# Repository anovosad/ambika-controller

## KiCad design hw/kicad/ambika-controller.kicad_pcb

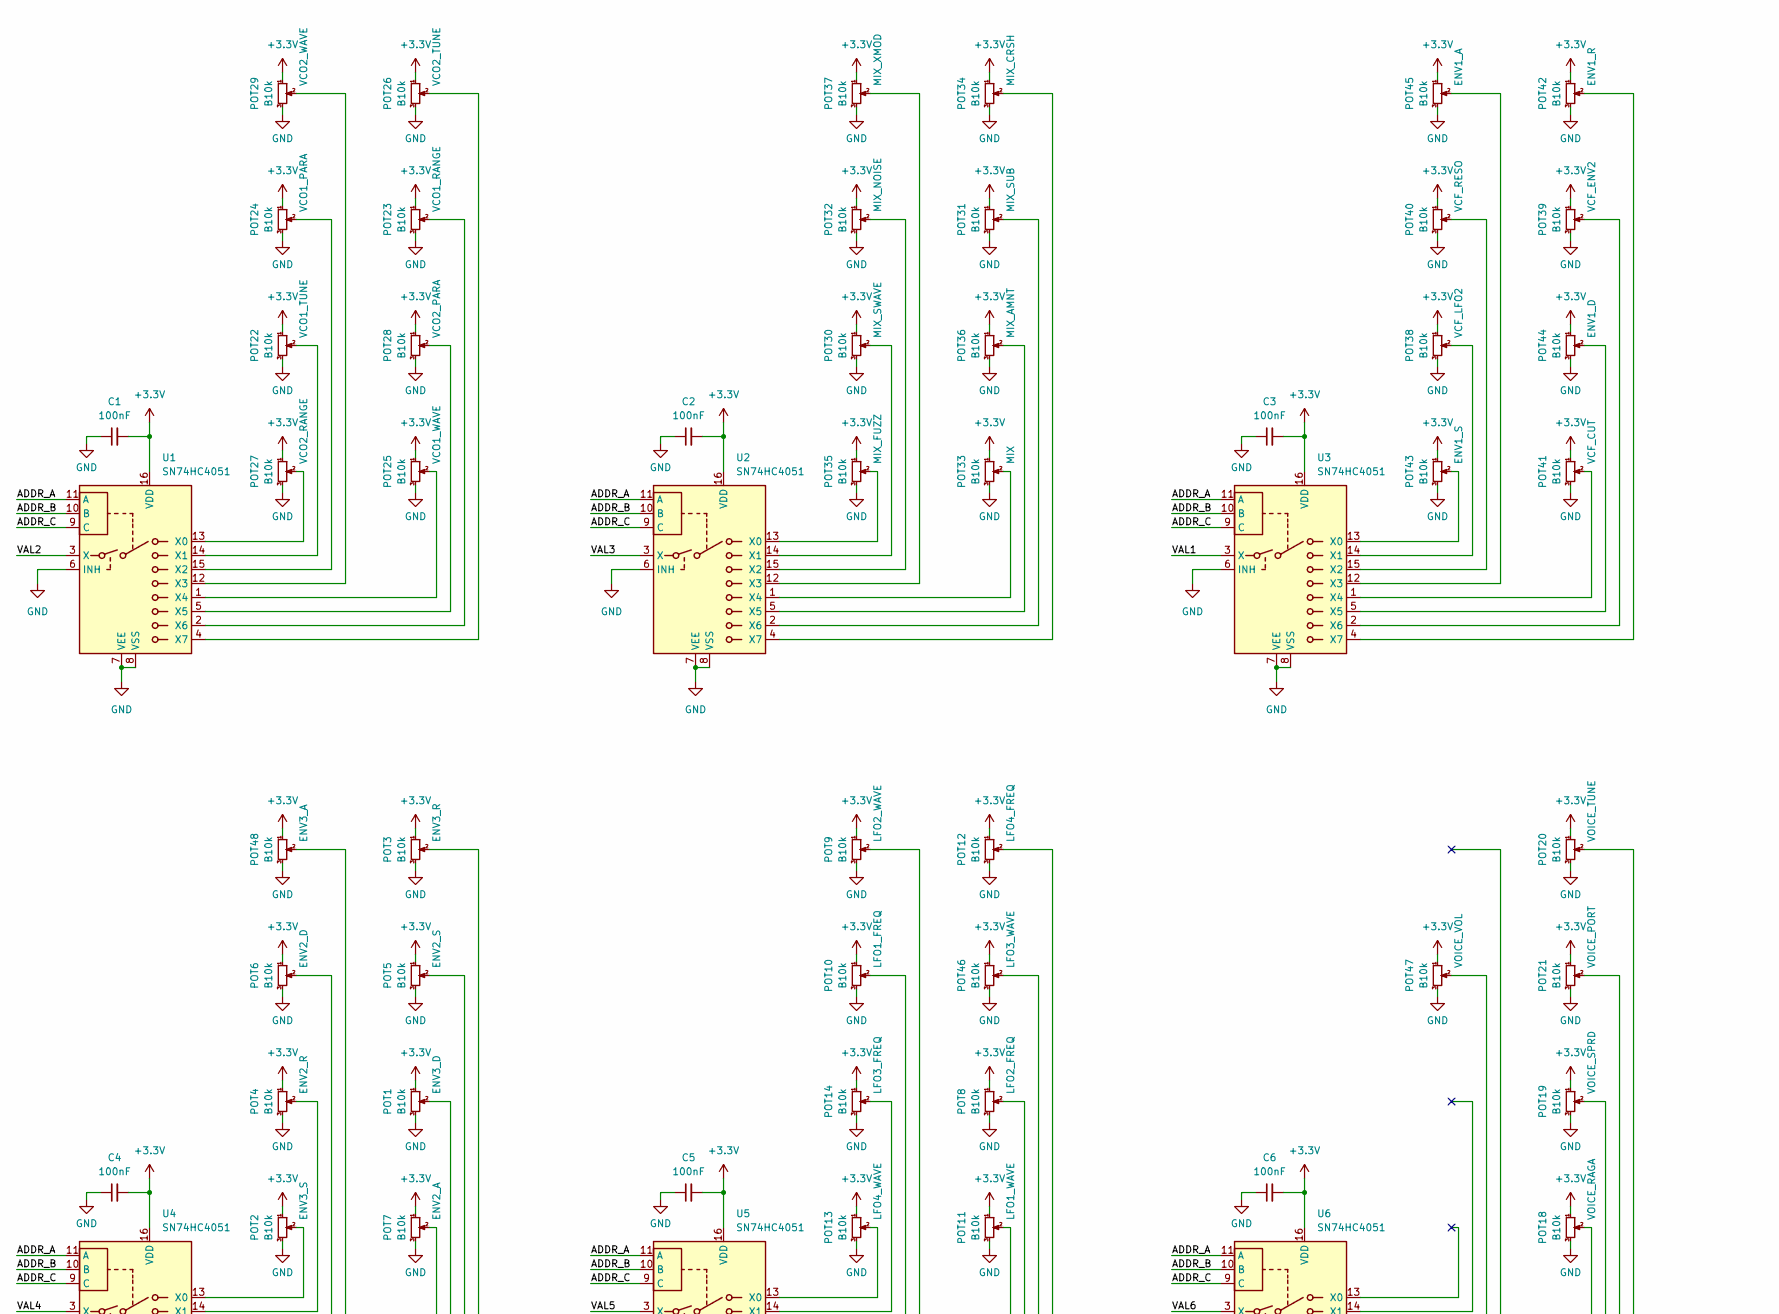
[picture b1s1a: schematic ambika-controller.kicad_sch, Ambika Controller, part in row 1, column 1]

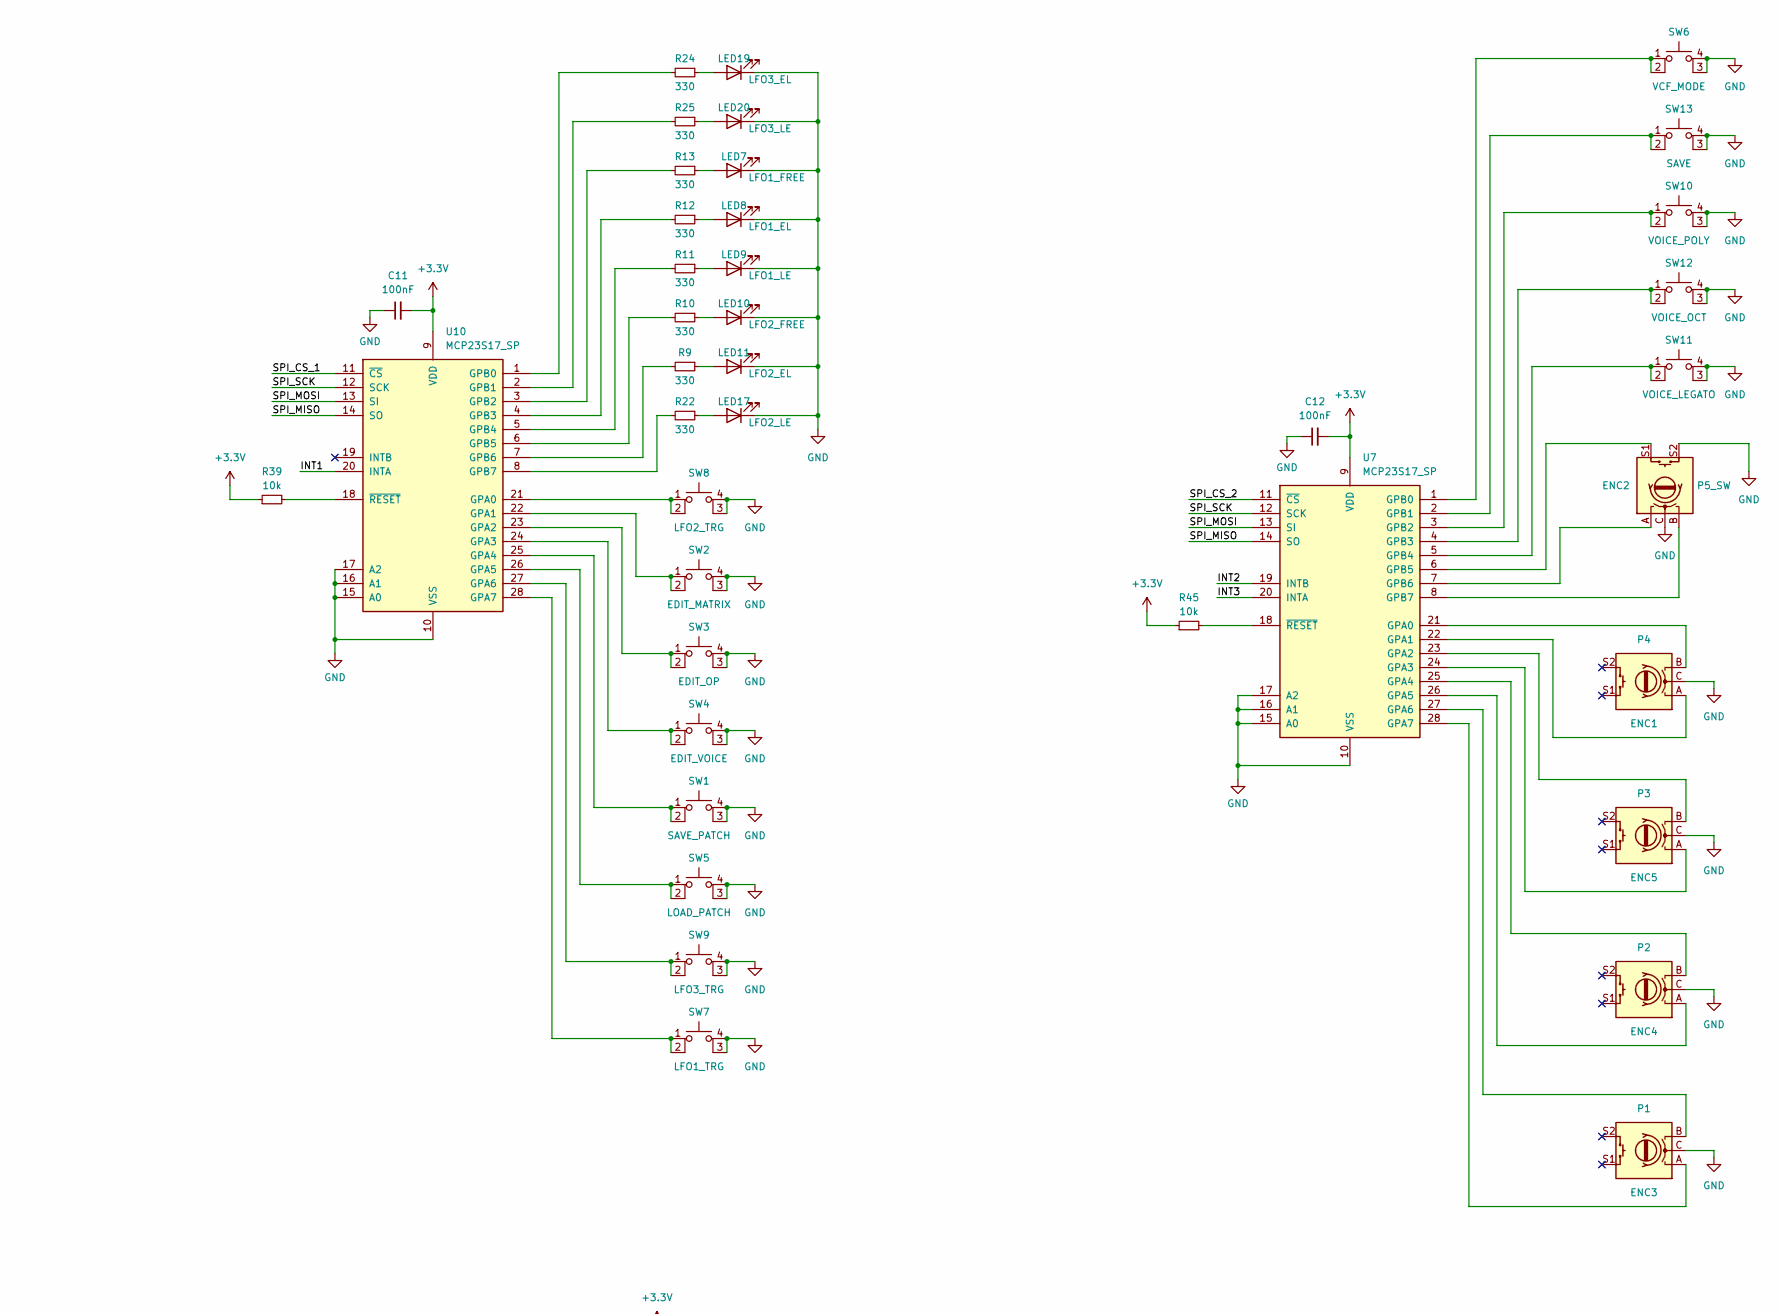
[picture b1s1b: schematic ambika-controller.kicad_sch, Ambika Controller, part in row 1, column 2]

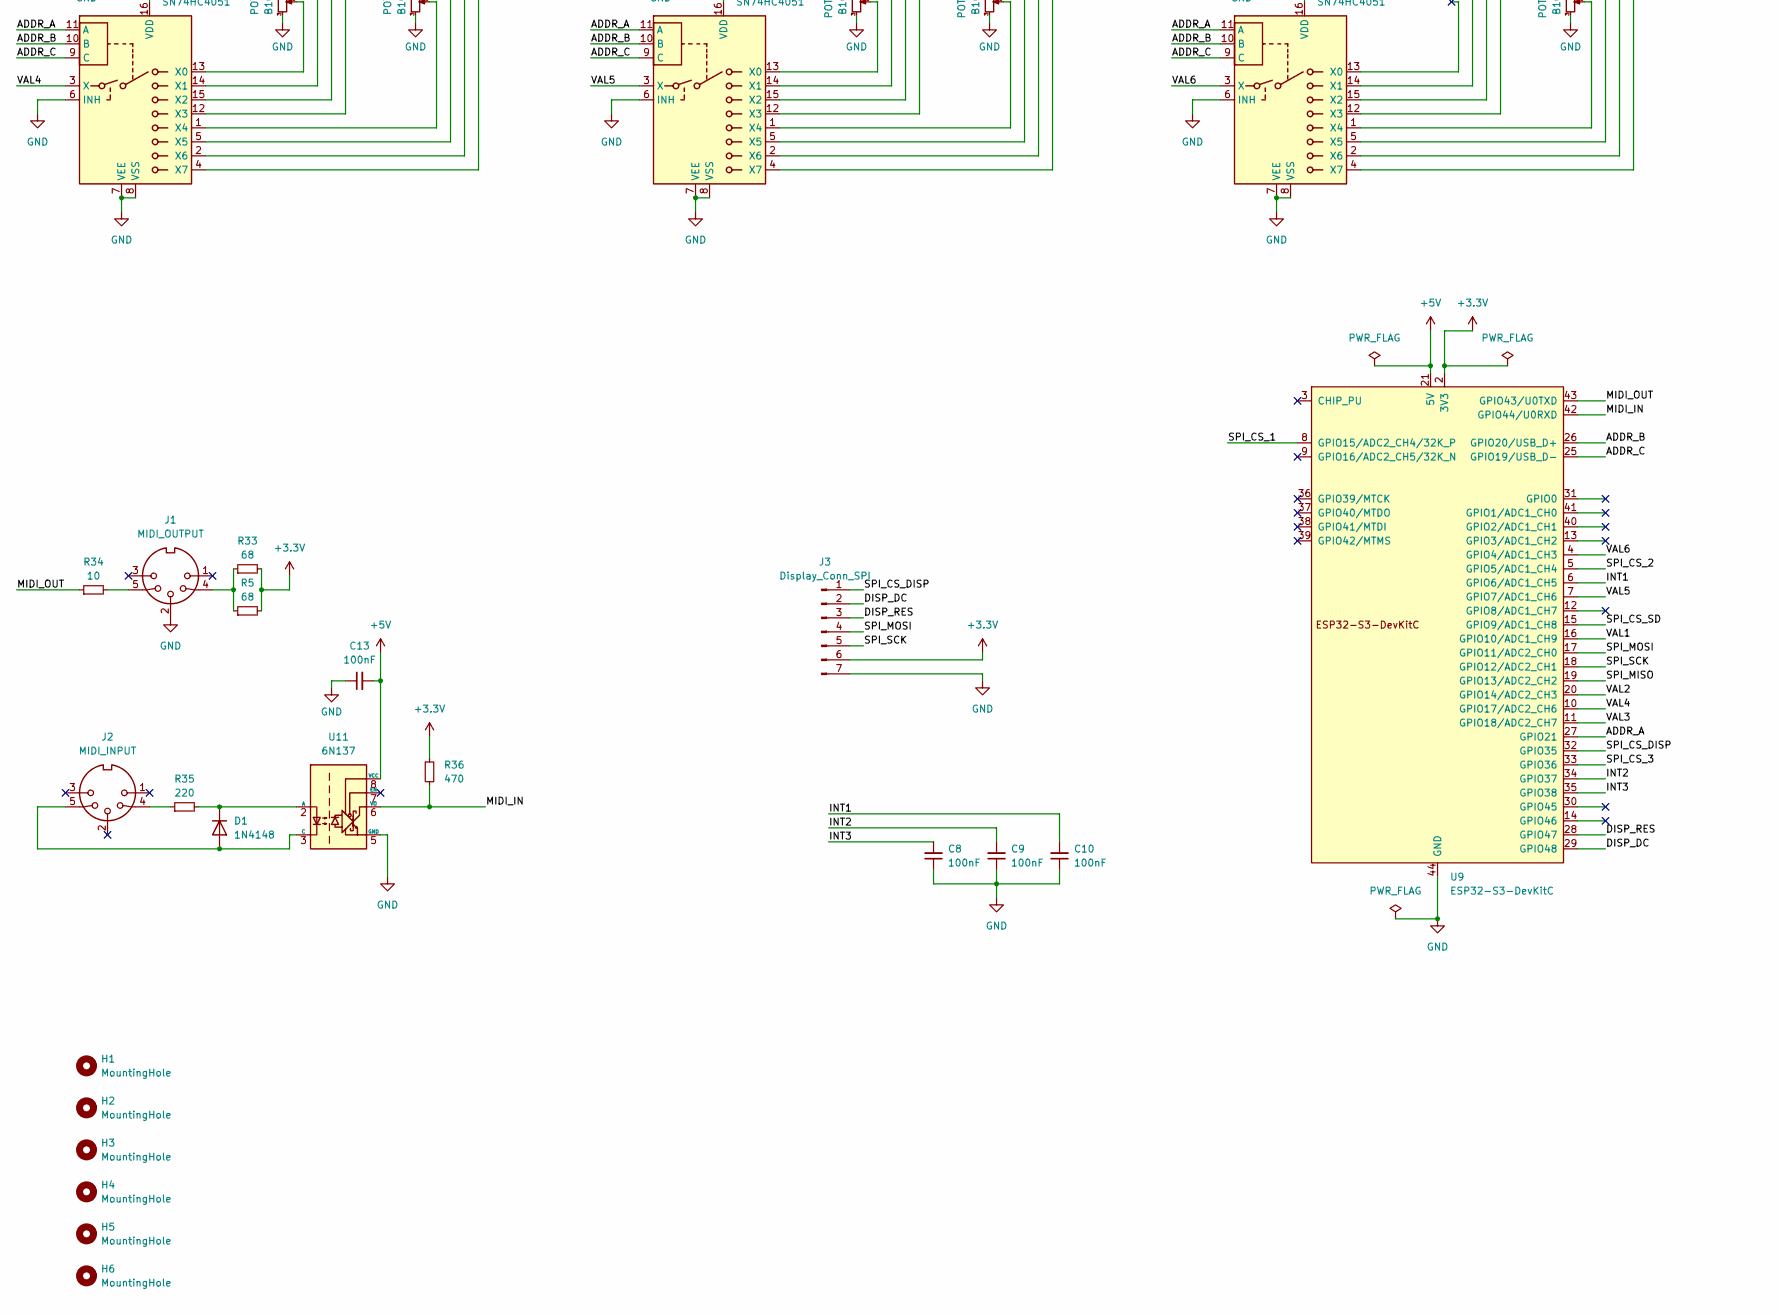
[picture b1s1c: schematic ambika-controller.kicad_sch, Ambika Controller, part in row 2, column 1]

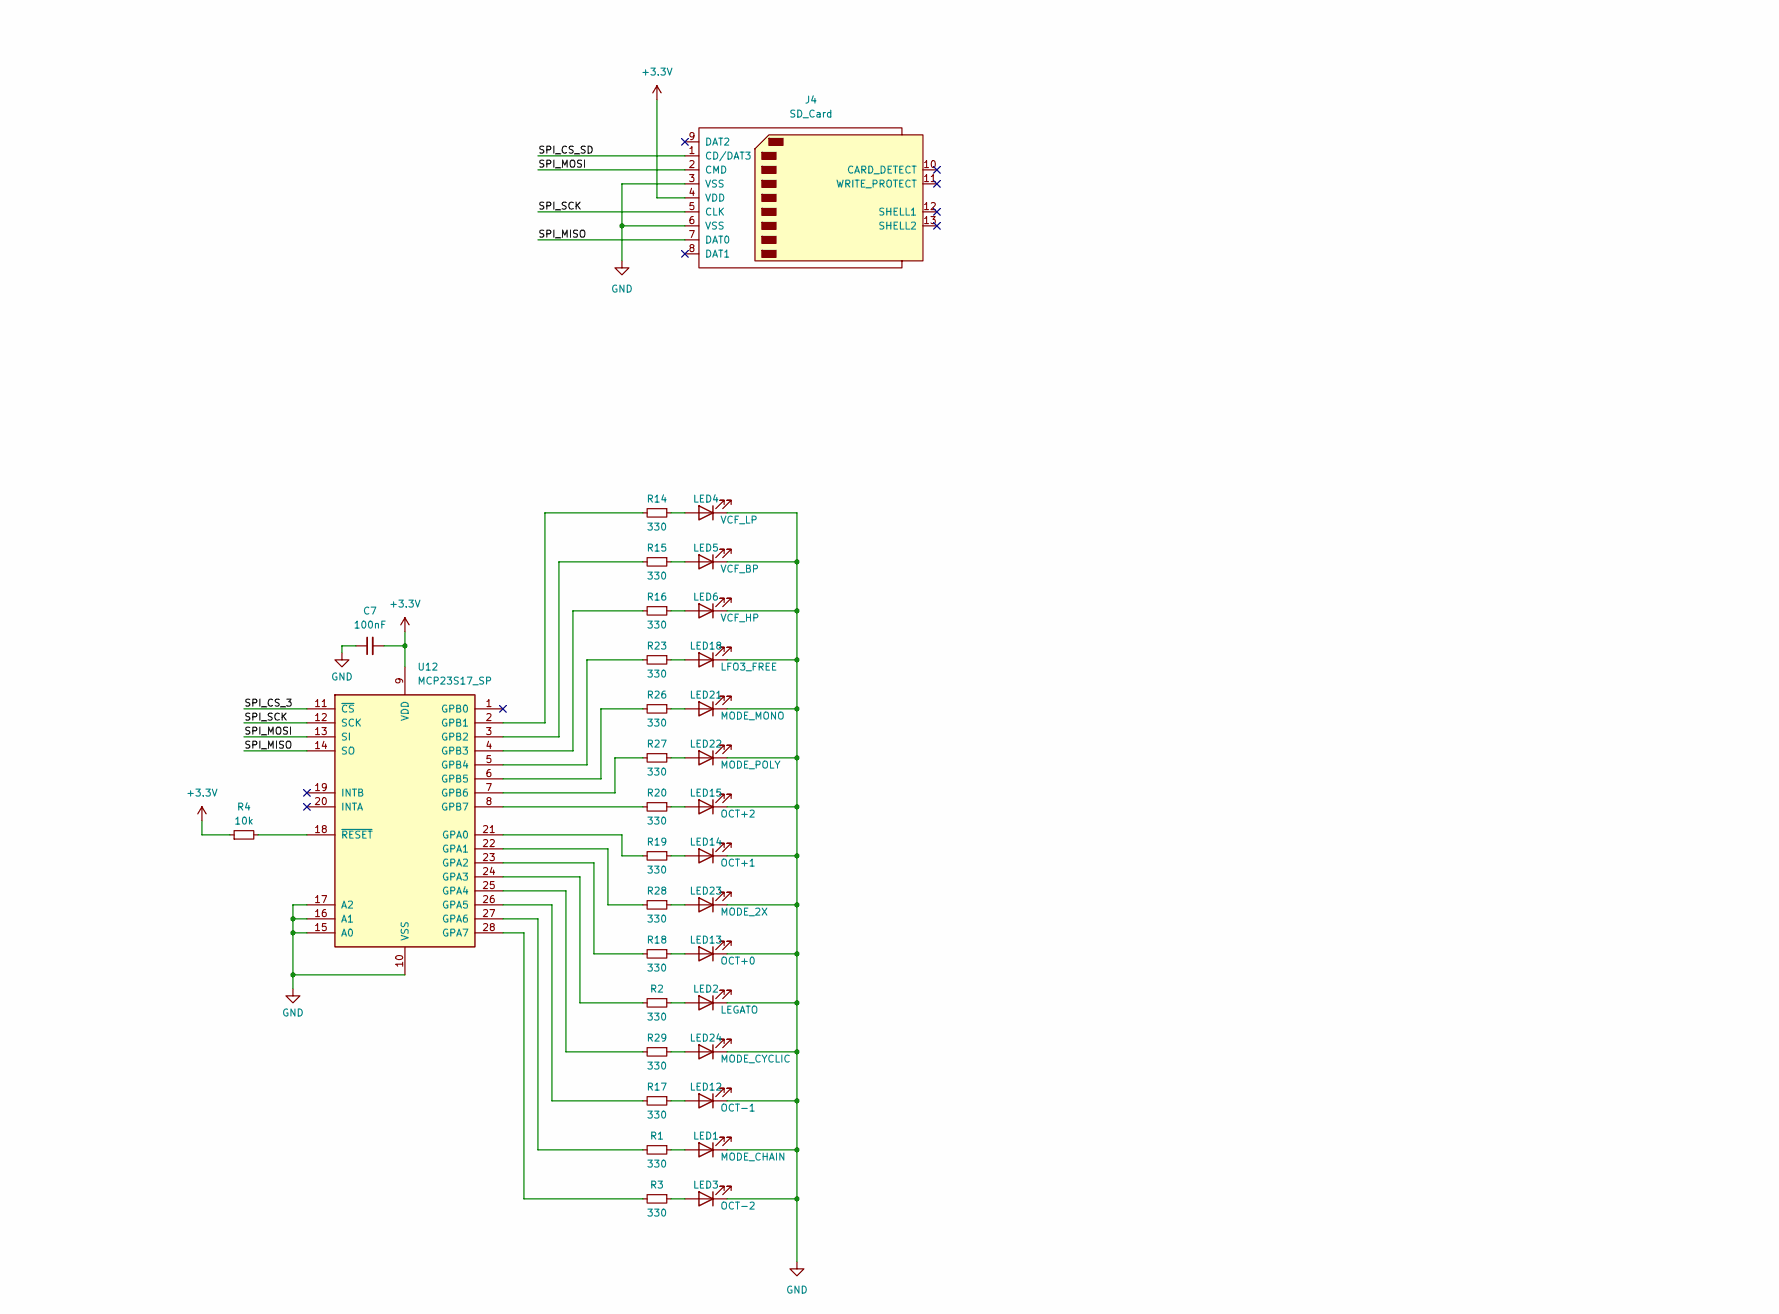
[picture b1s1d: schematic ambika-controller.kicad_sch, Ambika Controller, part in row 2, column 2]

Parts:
C1, C2, C3, C4, C5, C6, C7, C8, C9, C10, C11, C12, C13: 100nF; C_Disc_D5.0mm_W2.5mm_P2.50mm
D1: 1N4148; D_DO-35_SOD27_P7.62mm_Horizontal
ENC1, ENC2, ENC3, ENC4, ENC5: ROTARY_ENCODER; RotaryEncoder_Alps_EC12E-Switch_Vertical_H20mm
H1, H2, H3, H4, H5, H6: MountingHole; MountingHole_3.2mm_M3_DIN965_Pad_TopBottom
J1: MIDI_OUTPUT; MIDI_DIN5
J2: MIDI_INPUT; MIDI_DIN5
J3: Display_Conn_SPI; PinHeader_1x07_P2.54mm_Vertical
J4: SD_Card; SD_Kyocera_145638009511859+
LED1, LED2, LED3, LED4, LED5, LED6, LED7, LED8, LED9, LED10, LED11, LED12, LED13, LED14, LED15, LED17, LED18, LED19, LED20, LED21, LED22, LED23, LED24: GREEN; LED_D3.0mm
POT1, POT2, POT3, POT4, POT5, POT6, POT7, POT8, POT9, POT10, POT11, POT12, POT13, POT14, POT18, POT19, POT20, POT21, POT22, POT23, POT24, POT25, POT26, POT27, POT28, POT29, POT30, POT31, POT32, POT33, POT34, POT35, POT36, POT37, POT38, POT39, POT40, POT41, POT42, POT43, POT44, POT45, POT46, POT47, POT48: B10k; Potentiometer_Alpha_RD901F-40-00D_Single_Vertical
R1, R2, R3, R9, R10, R11, R12, R13, R14, R15, R16, R17, R18, R19, R20, R22, R23, R24, R25, R26, R27, R28, R29: 330; R_Axial_DIN0207_L6.3mm_D2.5mm_P7.62mm_Horizontal
R4, R39, R45: 10k; R_Axial_DIN0207_L6.3mm_D2.5mm_P7.62mm_Horizontal
R5, R33: 68; R_Axial_DIN0207_L6.3mm_D2.5mm_P7.62mm_Horizontal
R34: 10; R_Axial_DIN0207_L6.3mm_D2.5mm_P7.62mm_Horizontal
R35: 220; R_Axial_DIN0207_L6.3mm_D2.5mm_P7.62mm_Horizontal
R36: 470; R_Axial_DIN0207_L6.3mm_D2.5mm_P7.62mm_Horizontal
SW1, SW2, SW3, SW4, SW5, SW6, SW7, SW8, SW9, SW10, SW11, SW12, SW13: SW_PUSH-12mm-4pin
U1, U2, U3, U4, U5, U6: SN74HC4051; DIP-16_W7.62mm_Socket_LongPads
U7, U10, U12: MCP23S17_SP; DIP-28_W7.62mm
U9: ESP32-S3-DevKitC; Waveshare ESP32-S3-DevKitC
U11: 6N137; DIP-8_W7.62mm

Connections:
+3.3V: C1.2, C2.2, C3.2, C4.2, C5.2, C6.2, C7.2, C11.2, C12.2, J3.6, J4.4 (VDD), POT1.1, POT2.1, POT3.1, POT4.1, POT5.1, POT6.1, POT7.1, POT8.1, POT9.1, POT10.1, POT11.1, POT12.1, POT13.1, POT14.1, POT18.1, POT19.1, POT20.1, POT21.1, POT22.1, POT23.1, POT24.1, POT25.1, POT26.1, POT27.1, POT28.1, POT29.1, POT30.1, POT31.1, POT32.1, POT33.1, POT34.1, POT35.1, POT36.1, POT37.1, POT38.1, POT39.1, POT40.1, POT41.1, POT42.1, POT43.1, POT44.1, POT45.1, POT46.1, POT47.1, POT48.1, R4.1, R5.2, R33.2, R36.1, R39.1, R45.1, U1.16 (VDD), U2.16 (VDD), U3.16 (VDD), U4.16 (VDD), U5.16 (VDD), U6.16 (VDD), U7.9 (VDD), U9.1 (3V3), U9.2 (3V3), U10.9 (VDD), U12.9 (VDD)
+5V: C13.2, U9.21 (5V), U11.8 (VCC)
/ADDR_A: U1.11 (A), U2.11 (A), U3.11 (A), U4.11 (A), U5.11 (A), U6.11 (A), U9.27 (GPIO21)
/ADDR_B: U1.10 (B), U2.10 (B), U3.10 (B), U4.10 (B), U5.10 (B), U6.10 (B), U9.26 (GPIO20/USB_D+)
/ADDR_C: U1.9 (C), U2.9 (C), U3.9 (C), U4.9 (C), U5.9 (C), U6.9 (C), U9.25 (GPIO19/USB_D-)
/DISP_DC: J3.2, U9.29 (GPIO48)
/DISP_RES: J3.3, U9.28 (GPIO47)
/INT1: C10.2, U9.6 (GPIO6/ADC1_CH5), U10.20 (INTA)
/INT2: C9.2, U7.19 (INTB), U9.34 (GPIO37)
/INT3: C8.2, U7.20 (INTA), U9.35 (GPIO38)
/MIDI_IN: R36.2, U9.42 (GPIO44/U0RXD), U11.6 (VO)
/MIDI_OUT: R34.1, U9.43 (GPIO43/U0TXD)
/SPI_CS_1: U9.8 (GPIO15/ADC2_CH4/32K_P), U10.11 (~CS)
/SPI_CS_2: U7.11 (~CS), U9.5 (GPIO5/ADC1_CH4)
/SPI_CS_3: U9.33 (GPIO36), U12.11 (~CS)
/SPI_CS_DISP: J3.1, U9.32 (GPIO35)
/SPI_CS_SD: J4.1 (CD/DAT3), U9.15 (GPIO9/ADC1_CH8)
/SPI_MISO: J4.7 (DAT0), U7.14 (SO), U9.19 (GPIO13/ADC2_CH2), U10.14 (SO), U12.14 (SO)
/SPI_MOSI: J3.4, J4.2 (CMD), U7.13 (SI), U9.17 (GPIO11/ADC2_CH0), U10.13 (SI), U12.13 (SI)
/SPI_SCK: J3.5, J4.5 (CLK), U7.12 (SCK), U9.18 (GPIO12/ADC2_CH1), U10.12 (SCK), U12.12 (SCK)
/VAL1: U3.3 (X), U9.16 (GPIO10/ADC1_CH9)
/VAL2: U1.3 (X), U9.20 (GPIO14/ADC2_CH3)
/VAL3: U2.3 (X), U9.11 (GPIO18/ADC2_CH7)
/VAL4: U4.3 (X), U9.10 (GPIO17/ADC2_CH6)
/VAL5: U5.3 (X), U9.7 (GPIO7/ADC1_CH6)
/VAL6: U6.3 (X), U9.4 (GPIO4/ADC1_CH3)
GND: C1.1, C2.1, C3.1, C4.1, C5.1, C6.1, C7.1, C8.1, C9.1, C10.1, C11.1, C12.1, C13.1, ENC1.C, ENC2.C, ENC2.S2, ENC3.C, ENC4.C, ENC5.C, J1.2, J3.7, J4.3 (VSS), J4.6 (VSS), LED1.1 (K), LED2.1 (K), LED3.1 (K), LED4.1 (K), LED5.1 (K), LED6.1 (K), LED7.1 (K), LED8.1 (K), LED9.1 (K), LED10.1 (K), LED11.1 (K), LED12.1 (K), LED13.1 (K), LED14.1 (K), LED15.1 (K), LED17.1 (K), LED18.1 (K), LED19.1 (K), LED20.1 (K), LED21.1 (K), LED22.1 (K), LED23.1 (K), LED24.1 (K), POT1.3, POT2.3, POT3.3, POT4.3, POT5.3, POT6.3, POT7.3, POT8.3, POT9.3, POT10.3, POT11.3, POT12.3, POT13.3, POT14.3, POT18.3, POT19.3, POT20.3, POT21.3, POT22.3, POT23.3, POT24.3, POT25.3, POT26.3, POT27.3, POT28.3, POT29.3, POT30.3, POT31.3, POT32.3, POT33.3, POT34.3, POT35.3, POT36.3, POT37.3, POT38.3, POT39.3, POT40.3, POT41.3, POT42.3, POT43.3, POT44.3, POT45.3, POT46.3, POT47.3, POT48.3, SW1.3 (K), SW1.4 (A), SW2.3 (K), SW2.4 (A), SW3.3 (K), SW3.4 (A), SW4.3 (K), SW4.4 (A), SW5.3 (K), SW5.4 (A), SW6.3 (K), SW6.4 (A), SW7.3 (K), SW7.4 (A), SW8.3 (K), SW8.4 (A), SW9.3 (K), SW9.4 (A), SW10.3 (K), SW10.4 (A), SW11.3 (K), SW11.4 (A), SW12.3 (K), SW12.4 (A), SW13.3 (K), SW13.4 (A), U1.6 (INH), U1.7 (VEE), U1.8 (VSS), U2.6 (INH), U2.7 (VEE), U2.8 (VSS), U3.6 (INH), U3.7 (VEE), U3.8 (VSS), U4.6 (INH), U4.7 (VEE), U4.8 (VSS), U5.6 (INH), U5.7 (VEE), U5.8 (VSS), U6.6 (INH), U6.7 (VEE), U6.8 (VSS), U7.10 (VSS), U7.15 (A0), U7.16 (A1), U7.17 (A2), U9.22 (GND), U9.23 (GND), U9.24 (GND), U9.44 (GND), U10.10 (VSS), U10.15 (A0), U10.16 (A1), U10.17 (A2), U11.5 (GND), U12.10 (VSS), U12.15 (A0), U12.16 (A1), U12.17 (A2)
unnamed: D1.2 (A), J2.5, U11.3 (C)
unnamed: D1.1 (K), R35.2, U11.2 (A)
unnamed: J1.4, R5.1, R33.1
unnamed: J1.5, R34.2
unnamed: J2.4, R35.1
unnamed: LED1.2 (A), R1.1
unnamed: LED2.2 (A), R2.1
unnamed: LED3.2 (A), R3.1
unnamed: LED4.2 (A), R14.1
unnamed: LED5.2 (A), R15.1
unnamed: LED6.2 (A), R16.1
unnamed: LED7.2 (A), R13.1
unnamed: LED8.2 (A), R12.1
unnamed: LED9.2 (A), R11.1
unnamed: LED10.2 (A), R10.1
unnamed: LED11.2 (A), R9.1
unnamed: LED12.2 (A), R17.1
unnamed: LED13.2 (A), R18.1
unnamed: LED14.2 (A), R19.1
unnamed: LED15.2 (A), R20.1
unnamed: LED17.2 (A), R22.1
unnamed: LED18.2 (A), R23.1
unnamed: LED19.2 (A), R24.1
unnamed: LED20.2 (A), R25.1
unnamed: LED21.2 (A), R26.1
unnamed: LED22.2 (A), R27.1
unnamed: LED23.2 (A), R28.1
unnamed: LED24.2 (A), R29.1
unnamed: POT27.2, U1.13 (X0)
unnamed: POT22.2, U1.14 (X1)
unnamed: POT24.2, U1.15 (X2)
unnamed: POT29.2, U1.12 (X3)
unnamed: POT25.2, U1.1 (X4)
unnamed: POT28.2, U1.5 (X5)
unnamed: POT23.2, U1.2 (X6)
unnamed: POT26.2, U1.4 (X7)
unnamed: POT35.2, U2.13 (X0)
unnamed: POT30.2, U2.14 (X1)
unnamed: POT32.2, U2.15 (X2)
unnamed: POT37.2, U2.12 (X3)
unnamed: POT33.2, U2.1 (X4)
unnamed: POT36.2, U2.5 (X5)
unnamed: POT31.2, U2.2 (X6)
unnamed: POT34.2, U2.4 (X7)
unnamed: POT43.2, U3.13 (X0)
unnamed: POT38.2, U3.14 (X1)
unnamed: POT40.2, U3.15 (X2)
unnamed: POT45.2, U3.12 (X3)
unnamed: POT41.2, U3.1 (X4)
unnamed: POT44.2, U3.5 (X5)
unnamed: POT39.2, U3.2 (X6)
unnamed: POT42.2, U3.4 (X7)
unnamed: POT2.2, U4.13 (X0)
unnamed: POT4.2, U4.14 (X1)
unnamed: POT6.2, U4.15 (X2)
unnamed: POT48.2, U4.12 (X3)
unnamed: POT7.2, U4.1 (X4)
unnamed: POT1.2, U4.5 (X5)
unnamed: POT5.2, U4.2 (X6)
unnamed: POT3.2, U4.4 (X7)
unnamed: POT13.2, U5.13 (X0)
unnamed: POT14.2, U5.14 (X1)
unnamed: POT10.2, U5.15 (X2)
unnamed: POT9.2, U5.12 (X3)
unnamed: POT11.2, U5.1 (X4)
unnamed: POT8.2, U5.5 (X5)
unnamed: POT46.2, U5.2 (X6)
unnamed: POT12.2, U5.4 (X7)
unnamed: POT47.2, U6.15 (X2)
unnamed: POT18.2, U6.1 (X4)
unnamed: POT19.2, U6.5 (X5)
unnamed: POT21.2, U6.2 (X6)
unnamed: POT20.2, U6.4 (X7)
unnamed: ENC1.B, U7.21 (GPA0)
unnamed: ENC1.A, U7.22 (GPA1)
unnamed: ENC5.B, U7.23 (GPA2)
unnamed: ENC5.A, U7.24 (GPA3)
unnamed: ENC4.B, U7.25 (GPA4)
unnamed: ENC4.A, U7.26 (GPA5)
unnamed: ENC3.B, U7.27 (GPA6)
unnamed: ENC3.A, U7.28 (GPA7)
unnamed: SW6.1, SW6.2, U7.1 (GPB0)
unnamed: SW13.1, SW13.2, U7.2 (GPB1)
unnamed: SW10.1, SW10.2, U7.3 (GPB2)
unnamed: SW12.1, SW12.2, U7.4 (GPB3)
unnamed: SW11.1, SW11.2, U7.5 (GPB4)
unnamed: ENC2.S1, U7.6 (GPB5)
unnamed: ENC2.A, U7.7 (GPB6)
unnamed: ENC2.B, U7.8 (GPB7)
unnamed: R45.2, U7.18 (~RESET)
unnamed: SW8.1, SW8.2, U10.21 (GPA0)
unnamed: SW2.1, SW2.2, U10.22 (GPA1)
unnamed: SW3.1, SW3.2, U10.23 (GPA2)
unnamed: SW4.1, SW4.2, U10.24 (GPA3)
unnamed: SW1.1, SW1.2, U10.25 (GPA4)
unnamed: SW5.1, SW5.2, U10.26 (GPA5)
unnamed: SW9.1, SW9.2, U10.27 (GPA6)
unnamed: SW7.1, SW7.2, U10.28 (GPA7)
unnamed: R24.2, U10.1 (GPB0)
unnamed: R25.2, U10.2 (GPB1)
unnamed: R13.2, U10.3 (GPB2)
unnamed: R12.2, U10.4 (GPB3)
unnamed: R11.2, U10.5 (GPB4)
unnamed: R10.2, U10.6 (GPB5)
unnamed: R9.2, U10.7 (GPB6)
unnamed: R22.2, U10.8 (GPB7)
unnamed: R39.2, U10.18 (~RESET)
unnamed: R19.2, U12.21 (GPA0)
unnamed: R28.2, U12.22 (GPA1)
unnamed: R18.2, U12.23 (GPA2)
unnamed: R2.2, U12.24 (GPA3)
unnamed: R29.2, U12.25 (GPA4)
unnamed: R17.2, U12.26 (GPA5)
unnamed: R1.2, U12.27 (GPA6)
unnamed: R3.2, U12.28 (GPA7)
unnamed: R14.2, U12.2 (GPB1)
unnamed: R15.2, U12.3 (GPB2)
unnamed: R16.2, U12.4 (GPB3)
unnamed: R23.2, U12.5 (GPB4)
unnamed: R26.2, U12.6 (GPB5)
unnamed: R27.2, U12.7 (GPB6)
unnamed: R20.2, U12.8 (GPB7)
unnamed: R4.2, U12.18 (~RESET)

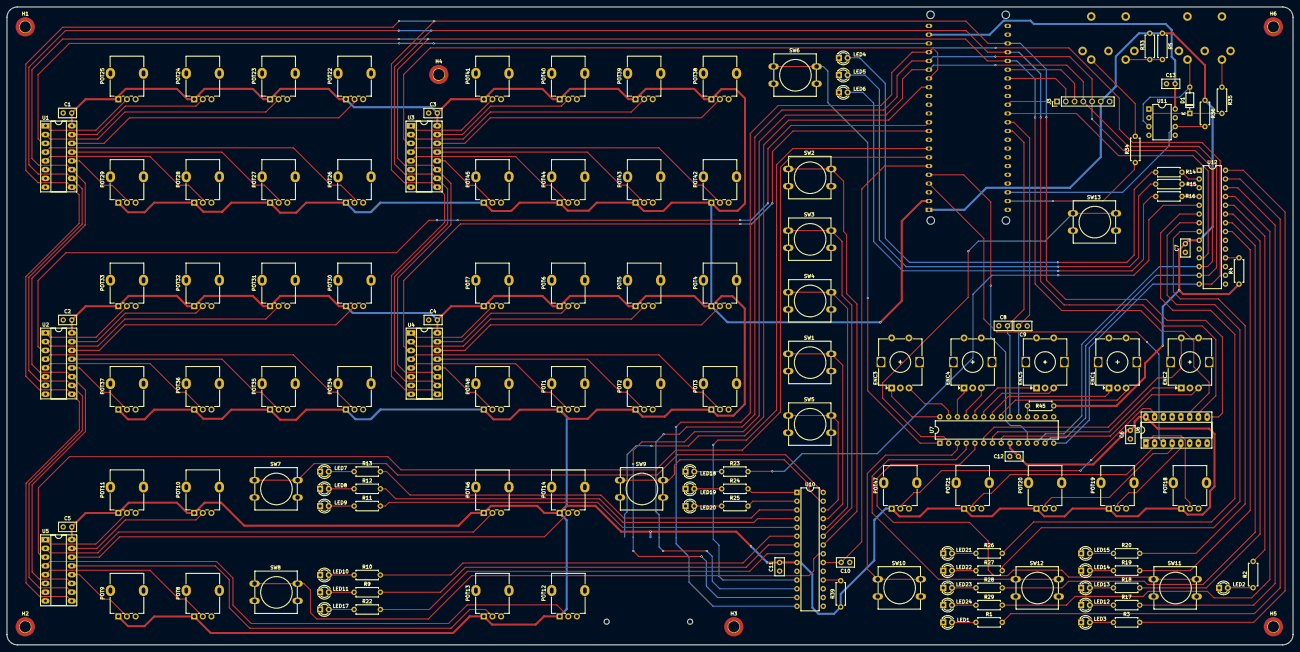
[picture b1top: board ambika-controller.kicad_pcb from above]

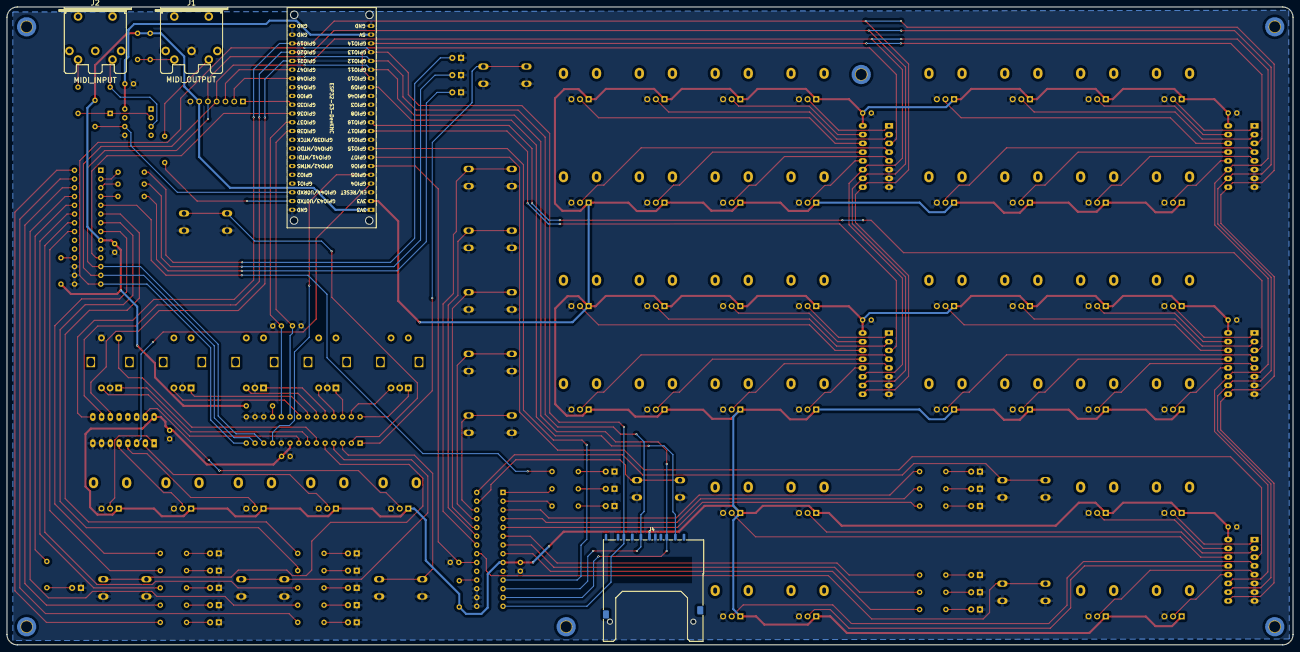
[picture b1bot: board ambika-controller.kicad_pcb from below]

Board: 2 copper layers, 373.0 x 185.0 mm, 152 parts (4 on the bottom side), 150 nets.

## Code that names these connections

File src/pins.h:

#pragma once

#define PIN_VAL1 10 
#define PIN_VAL2 14
#define PIN_VAL3 18
#define PIN_VAL4 17
#define PIN_VAL5 7
#define PIN_VAL6 4

#define PIN_ADDR_A 21
#define PIN_ADDR_B 20
#define PIN_ADDR_C 19

#define PIN_MCP1_CS 15
#define PIN_MCP2_CS 5
#define PIN_MCP3_CS 36

#define PIN_MCP_INT1 6
#define PIN_MCP_INT2 37
#define PIN_MCP_INT3 38

#define PIN_LED_VCF_LP 9
#define PIN_LED_VCF_BP 10
#define PIN_LED_VCF_HP 11

#define PIN_LED_OCT_PLUS2 15
#define PIN_LED_OCT_PLUS1 0
#define PIN_LED_OCT_0 2
#define PIN_LED_OCT_MINUS1 5
#define PIN_LED_OCT_MINUS2 7

#define PIN_LED_MODE_MONO 13
#define PIN_LED_MODE_POLY 14
#define PIN_LED_MODE_2X 1
#define PIN_LED_MODE_CYCLIC 4
#define PIN_LED_MODE_CHAIN 6

#define PIN_LED_LFO1_FREE 10
#define PIN_LED_LFO1_EL 11
#define PIN_LED_LFO1_LE 12

#define PIN_LED_LFO2_FREE 13
#define PIN_LED_LFO2_EL 14
#define PIN_LED_LFO2_LE 15

#define PIN_LED_LFO3_FREE 12
#define PIN_LED_LFO3_EL 8
#define PIN_LED_LFO3_LE 9

#define PIN_LED_LEGATO 3

#define PIN_SW_VCF_MODE 8
#define PIN_SW_SAVE 9
#define PIN_SW_VOICE_POLY 10
#define PIN_SW_VOICE_OCT 11
#define PIN_SW_VOICE_LEGATO 12
#define PIN_SW_ENC5 13
#define PIN_SW_LFO2_TRG 0
#define PIN_SW_MAIN_PAGE 1
#define PIN_SW_EDIT_MATRIX_OP 2
#define PIN_SW_EDIT_VOICE 3
#define PIN_SW_LOAD_PATCH 4
#define PIN_SW_SAVE_PATCH 5
#define PIN_SW_LFO3_TRG 6
#define PIN_SW_LFO1_TRG 7

#define PIN_ENC1_CW 6
#define PIN_ENC1_CCW 7
#define PIN_ENC2_CW 4
#define PIN_ENC2_CCW 5
#define PIN_ENC3_CW 2
#define PIN_ENC3_CCW 3
#define PIN_ENC4_CW 0
#define PIN_ENC4_CCW 1
#define PIN_ENC5_CW 15
#define PIN_ENC5_CCW 14
#define PIN_ENC5_BTN 13

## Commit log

2024-05-20 added kicad files
2024-06-11 change to esp32
2024-06-11 update scheme
2024-07-20 added sources
2024-07-20 changed switches behaviour
2024-07-23 added patch loading
2024-07-23 pages refactor
2024-07-23 sd refactor
